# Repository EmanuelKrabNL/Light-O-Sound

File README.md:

# Light-O-Sound
# Speaker or light? why not both!

# What does this project do?
this is a music reacting lightstrip, AND a bluetooth speaker in one!

# How does it work?
basically, it reads input, which reacts to the sound. so even if you latency is high, it will still sync perfectly with both the bluetooth and light.

# Why have i made this?
ive always wanted this to be honest, i also made this for half life hack club program.

schematic:

pcb:

3d (somewhat):

# Firmware setup
Install the Adafruit NeoPixel library using the Arduino IDE Library Manager. The VS Code C/C++ configuration expects it in the default Arduino libraries folder (`~/Arduino/libraries/Adafruit_NeoPixel`). If your Arduino sketchbook uses a different location, update the library path in `.vscode/c_cpp_properties.json`.

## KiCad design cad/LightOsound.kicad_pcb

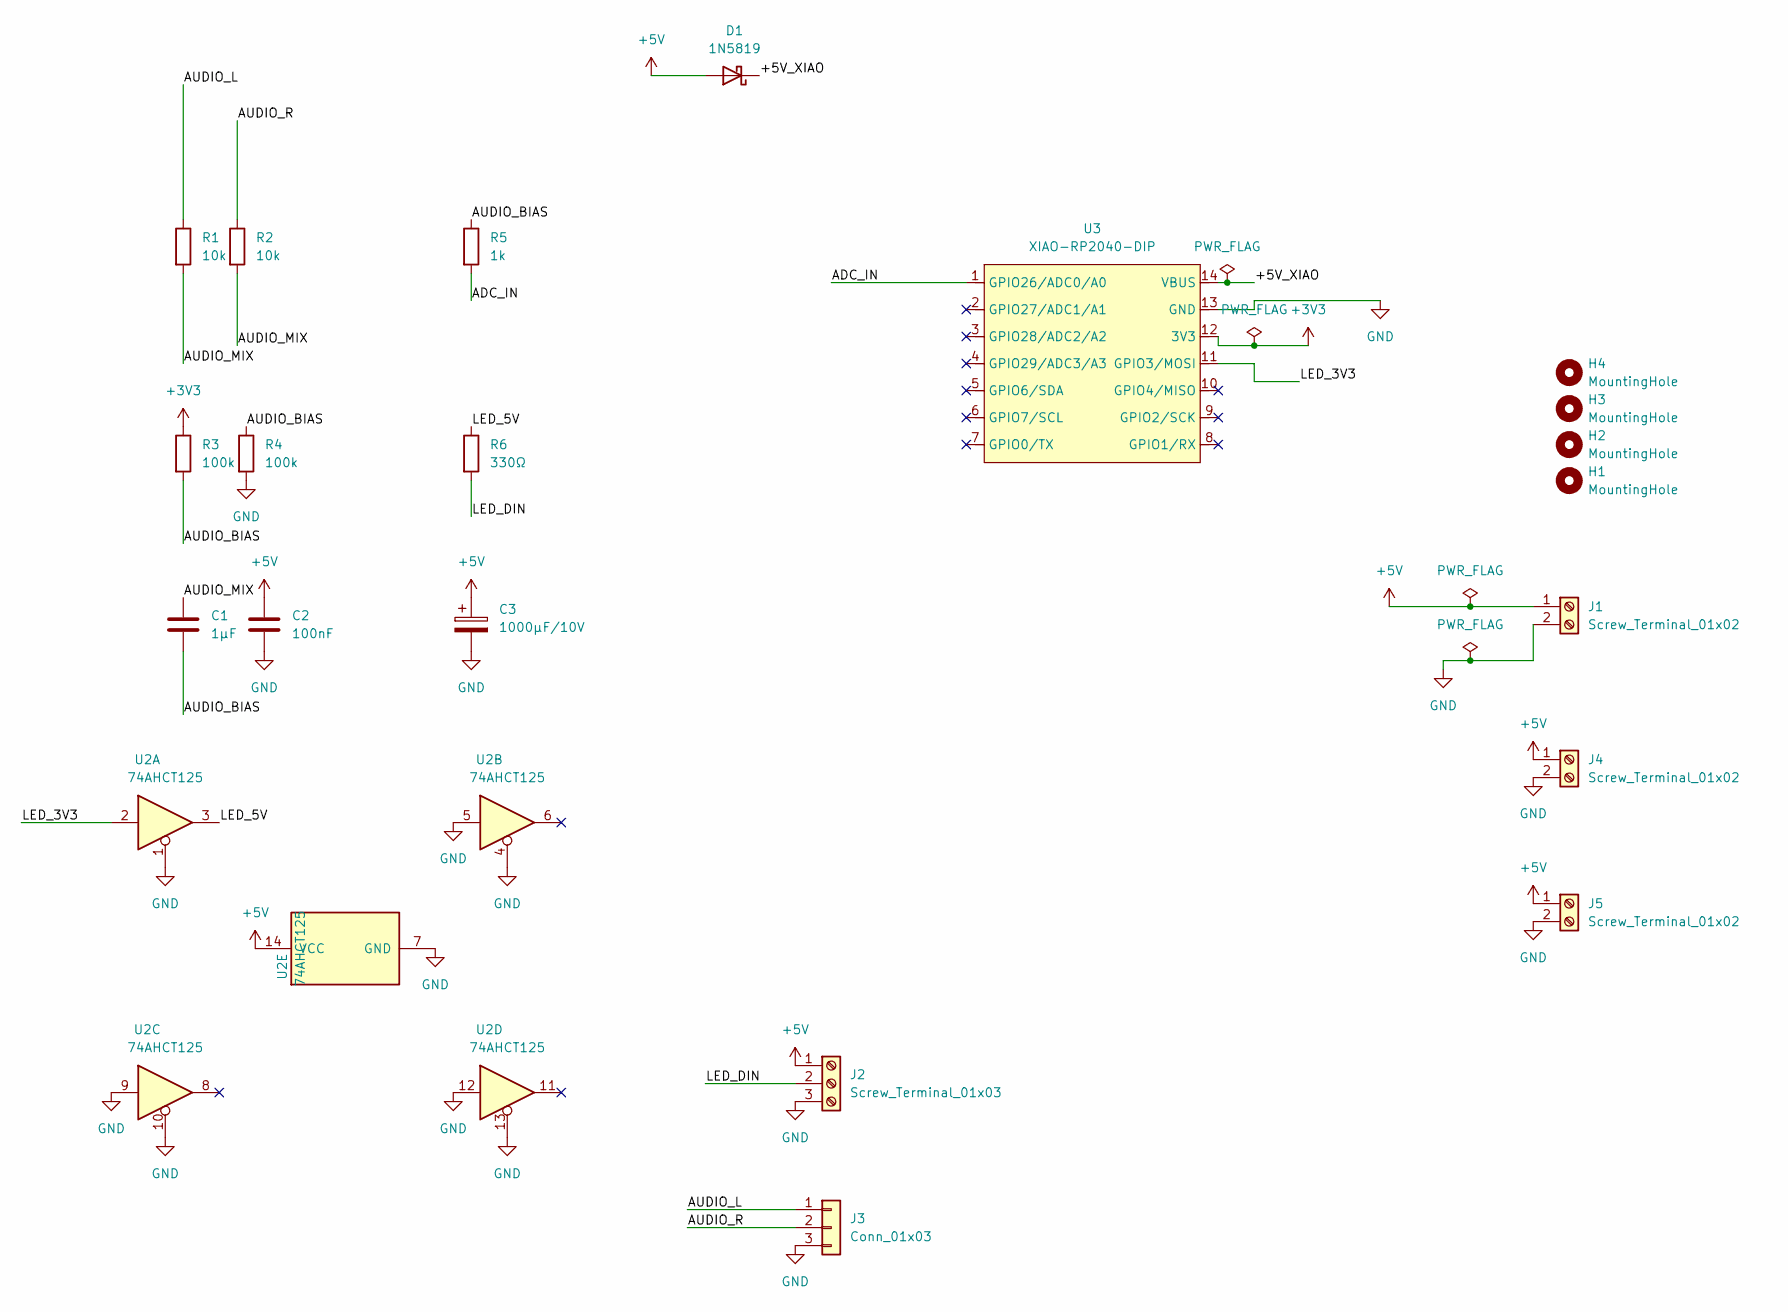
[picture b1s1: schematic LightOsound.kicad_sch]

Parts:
C1: 1µF; C_Disc_D5.0mm_W2.5mm_P5.00mm
C2: 100nF; C_Disc_D5.0mm_W2.5mm_P5.00mm
C3: 1000µF/10V; CP_Radial_D8.0mm_P3.50mm
D1: 1N5819; D_DO-41_SOD81_P10.16mm_Horizontal
H1, H2, H3, H4: MountingHole; MountingHole_3.2mm_M3
J1, J4, J5: Screw_Terminal_01x02; PinHeader_1x02_P2.54mm_Vertical
J2: Screw_Terminal_01x03; PinHeader_1x03_P2.54mm_Vertical
J3: Conn_01x03; PinHeader_1x03_P2.54mm_Vertical
R1, R2: 10k; R_Axial_DIN0207_L6.3mm_D2.5mm_P7.62mm_Horizontal
R3, R4: 100k; R_Axial_DIN0207_L6.3mm_D2.5mm_P7.62mm_Horizontal
R5: 1k; R_Axial_DIN0207_L6.3mm_D2.5mm_P7.62mm_Horizontal
R6: 330Ω; R_Axial_DIN0207_L6.3mm_D2.5mm_P7.62mm_Horizontal
U2: 74AHCT125; DIP-14_W7.62mm
U3: XIAO-RP2040-DIP

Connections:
+3V3: R3.1, U3.12 (3V3)
+5V: C2.1, C3.1, D1.2 (A), J1.1, J2.1, J4.1, J5.1, U2.14 (VCC)
/+5V_XIAO: D1.1 (K), U3.14 (VBUS)
/ADC_IN: R5.2, U3.1 (GPIO26/ADC0/A0)
/AUDIO_BIAS: C1.2, R3.2, R4.1, R5.1
/AUDIO_L: J3.1, R1.1
/AUDIO_MIX: C1.1, R1.2, R2.2
/AUDIO_R: J3.2, R2.1
/LED_3V3: U2.2, U3.11 (GPIO3/MOSI)
/LED_5V: R6.1, U2.3
/LED_DIN: J2.2, R6.2
GND: C2.2, C3.2, J1.2, J2.3, J3.3, J4.2, J5.2, R4.2, U2.1, U2.4, U2.5, U2.7 (GND), U2.9, U2.10, U2.12, U2.13, U3.13 (GND)

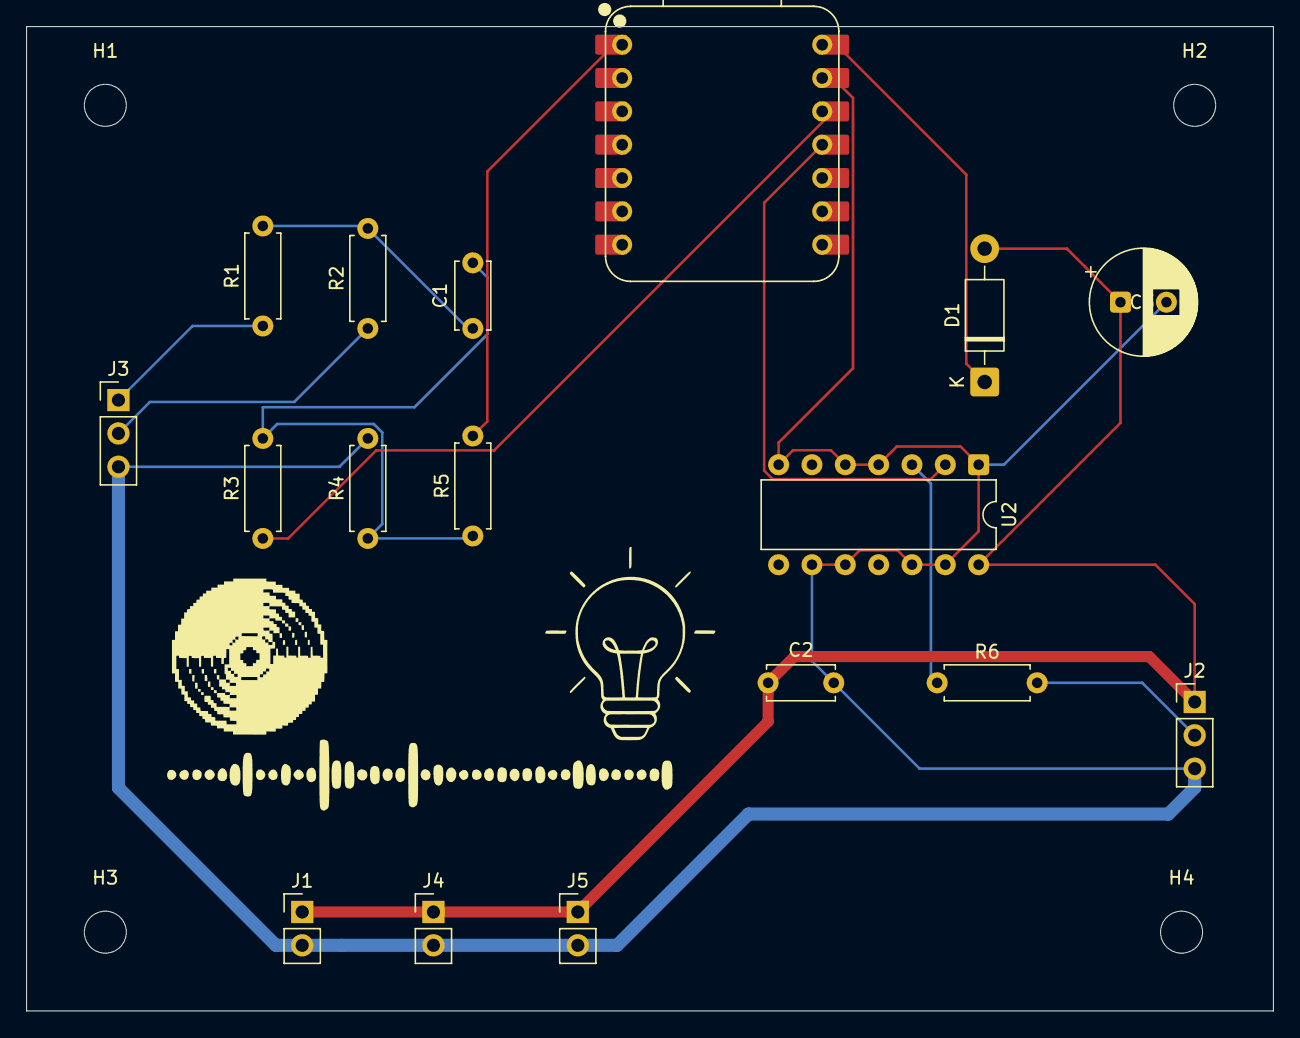
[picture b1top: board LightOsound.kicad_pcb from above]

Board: 2 copper layers, 95.0 x 75.0 mm, 21 parts (0 on the bottom side), 12 nets.

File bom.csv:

Designator,Footprint,Quantity,Value,LCSC Part #
C1,C_Disc_D5.0mm_W2.5mm_P5.00mm,1,1µF,
C2,C_Disc_D5.0mm_W2.5mm_P5.00mm,1,100nF,
C3,CP_Radial_D8.0mm_P3.50mm,1,1000µF/10V,
D1,D_DO-41_SOD81_P10.16mm_Horizontal,1,1N5819,
"J1, J4, J5",PinHeader_1x02_P2.54mm_Vertical,3,Screw_Terminal_01x02,
J2,PinHeader_1x03_P2.54mm_Vertical,1,Screw_Terminal_01x03,
J3,PinHeader_1x03_P2.54mm_Vertical,1,Conn_01x03,
"R1, R2",R_Axial_DIN0207_L6.3mm_D2.5mm_P7.62mm_Horizontal,2,10k,
"R3, R4",R_Axial_DIN0207_L6.3mm_D2.5mm_P7.62mm_Horizontal,2,100k,
R5,R_Axial_DIN0207_L6.3mm_D2.5mm_P7.62mm_Horizontal,1,1k,
R6,R_Axial_DIN0207_L6.3mm_D2.5mm_P7.62mm_Horizontal,1,330Ω,
U2,DIP-14_W7.62mm,1,74AHCT125,
U3,XIAO-RP2040-DIP,1,XIAO-RP2040-DIP,
